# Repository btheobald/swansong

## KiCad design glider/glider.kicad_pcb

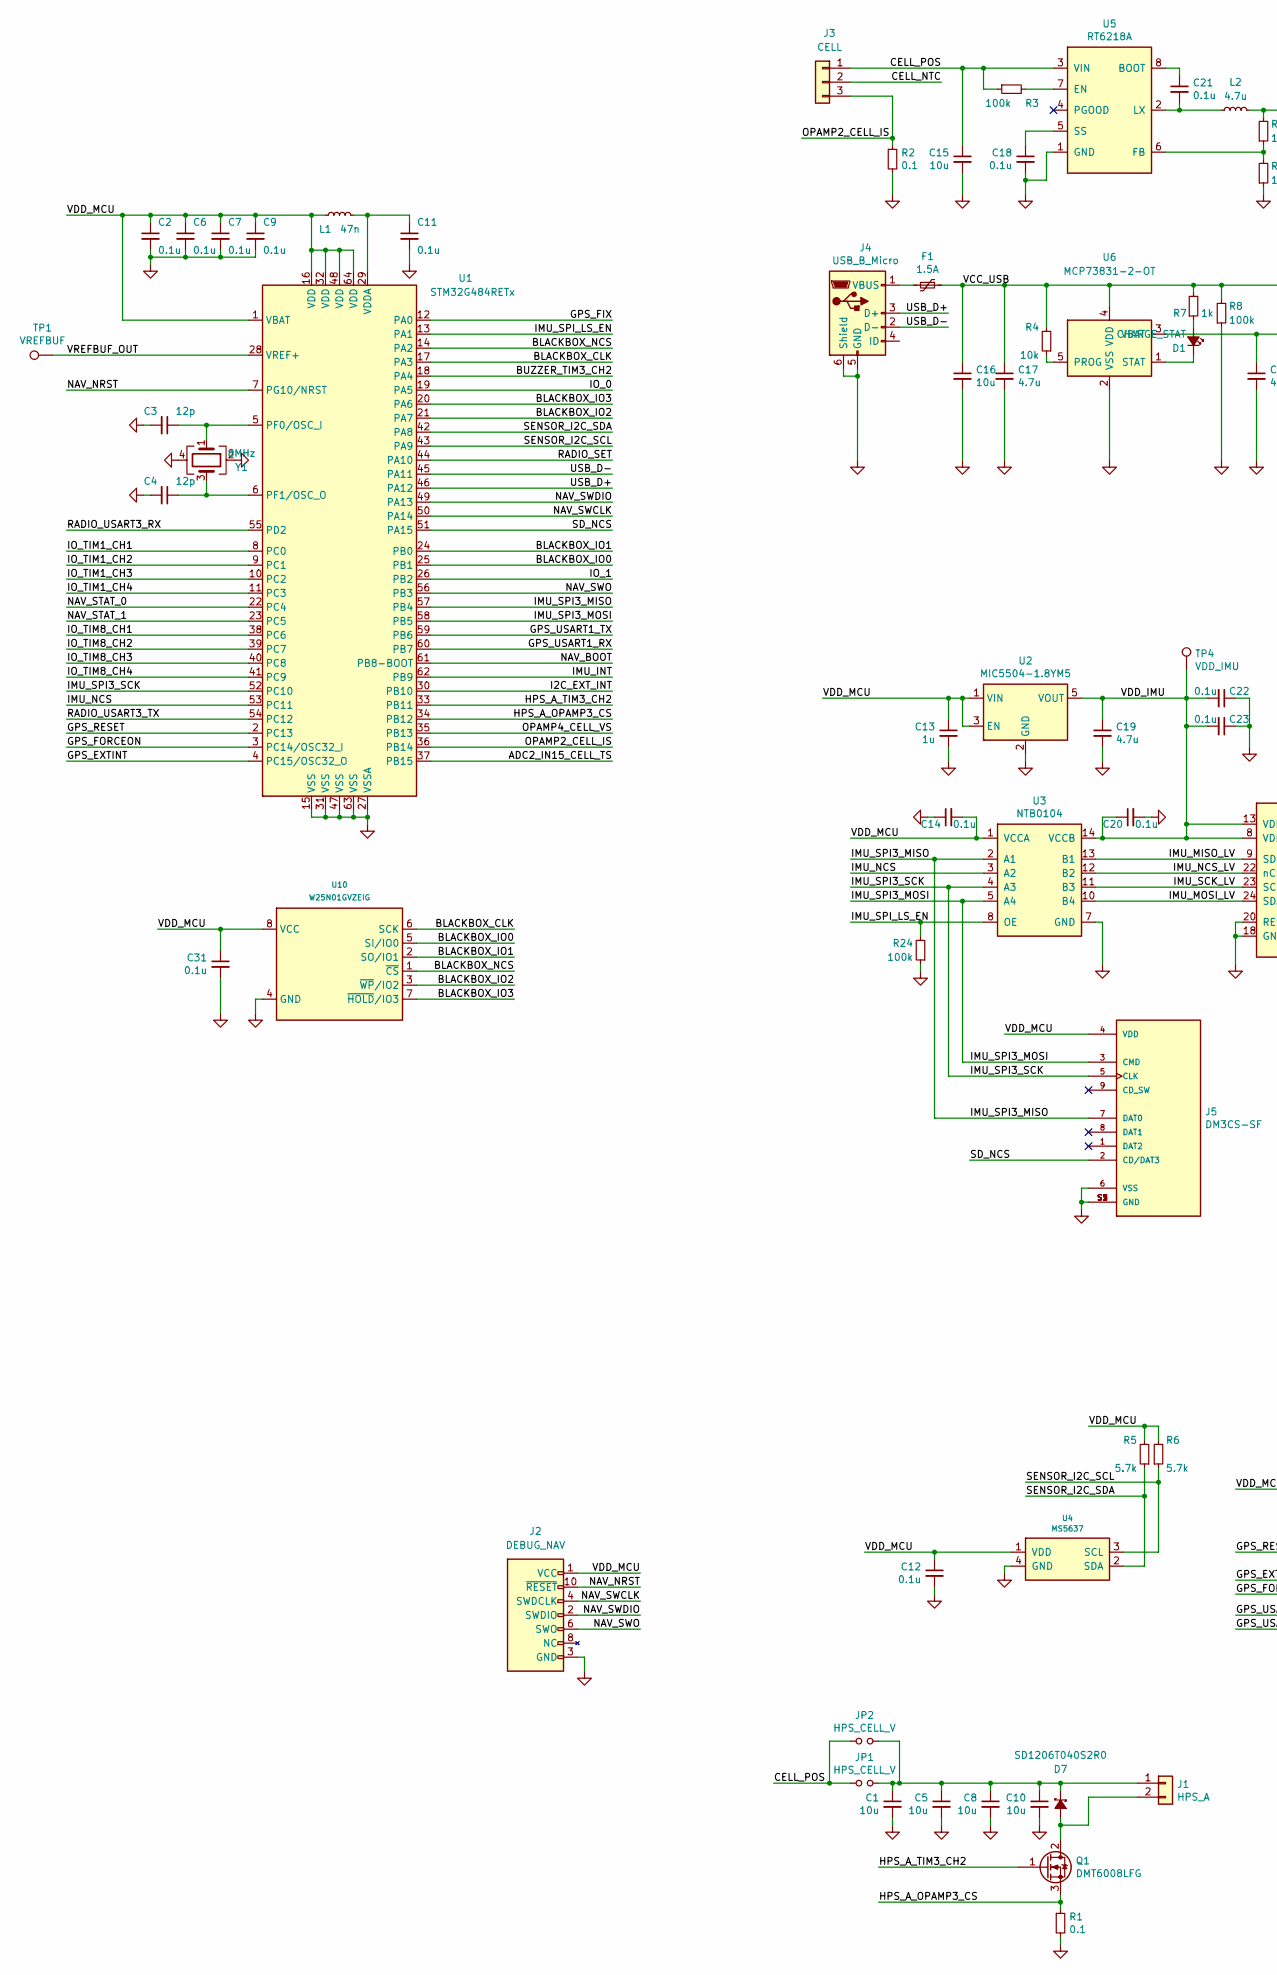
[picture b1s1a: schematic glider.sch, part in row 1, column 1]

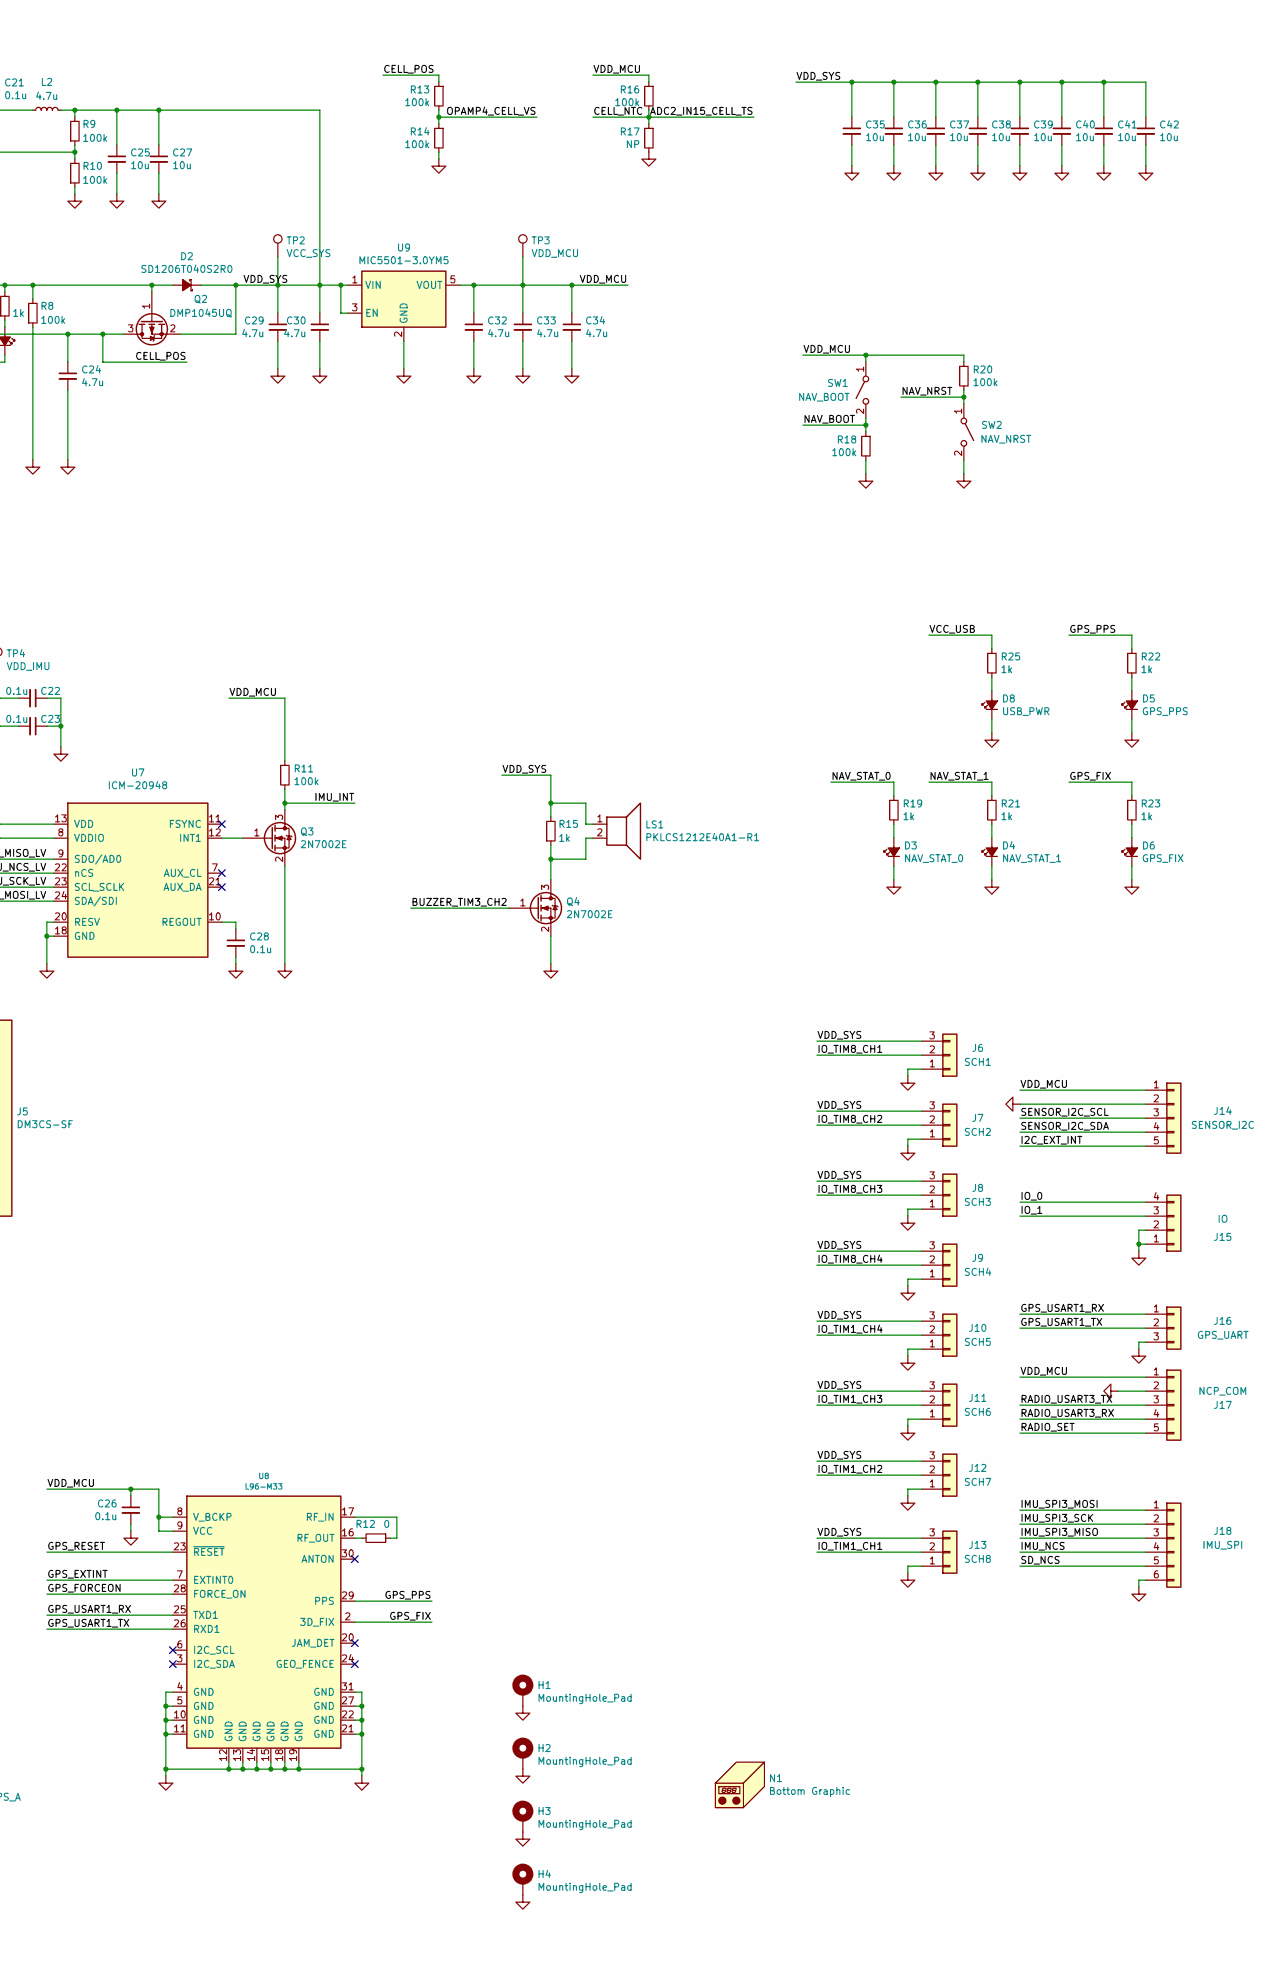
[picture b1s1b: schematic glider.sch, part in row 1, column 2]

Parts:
C1, C5, C8, C10: 10u; C_1206_3216Metric
C2, C6, C7, C9, C11, C12, C14, C18, C20, C21, C22, C23, C26, C28, C31: 0.1u; C_0402_1005Metric
C3, C4: 12p; C_0402_1005Metric
C13: 1u; C_0805_2012Metric
C15, C16, C25, C27, C35, C36, C37, C38, C39, C40, C41, C42: 10u; C_0805_2012Metric
C17, C19, C24, C29, C30, C32, C33, C34: 4.7u; C_0805_2012Metric
D1: CHARGE_STAT; LED_0603_1608Metric
D2, D7: SD1206T040S2R0; D_SOD-123
D3: NAV_STAT_0; LED_0603_1608Metric
D4: NAV_STAT_1; LED_0603_1608Metric
D5: GPS_PPS; LED_0603_1608Metric
D6: GPS_FIX; LED_0603_1608Metric
D8: USB_PWR; LED_0603_1608Metric
F1: 1.5A; R_1210_3225Metric
H1, H2, H3, H4: MountingHole_Pad; MountingHole_2.5mm_Pad_Via
J1: HPS_A; R_2816_7142Metric_Pad3.20x4.45mm_HandSolder
J2: DEBUG_NAV; PinHeader_2x05_P1.27mm_Vertical_SMD
J3: CELL; PinSocket_1x03_P2.54mm_Vertical
J4: USB_B_Micro; USB_Micro-B_Molex_47346-0001
J5: DM3CS-SF; HRS_DM3CS-SF; PARTREV n/a
J6: SCH1; PinHeader_1x03_P2.54mm_Vertical
J7: SCH2; PinHeader_1x03_P2.54mm_Vertical
J8: SCH3; PinHeader_1x03_P2.54mm_Vertical
J9: SCH4; PinHeader_1x03_P2.54mm_Vertical
J10: SCH5; PinHeader_1x03_P2.54mm_Vertical
J11: SCH6; PinHeader_1x03_P2.54mm_Vertical
J12: SCH7; PinHeader_1x03_P2.54mm_Vertical
J13: SCH8; PinHeader_1x03_P2.54mm_Vertical
J14: SENSOR_I2C; PinHeader_1x05_P2.54mm_Vertical
J15: IO; PinHeader_1x04_P1.27mm_Vertical
J16: GPS_UART; PinHeader_1x03_P1.27mm_Vertical
J17: NCP_COM; PinHeader_1x05_P2.54mm_Vertical
J18: IMU_SPI; PinHeader_1x06_P1.27mm_Vertical
JP1, JP2: HPS_CELL_V; SolderJumper-2_P1.3mm_Open_TrianglePad1.0x1.5mm
L1: 47n; L_0402_1005Metric
L2: 4.7u; L_Bourns-SRN4018
LS1: PKLCS1212E40A1-R1; PKLCS1212
N1: Bottom Graphic; boardartswift
Q1: DMT6008LFG; Diodes_PowerDI3333-8
Q2: DMP1045UQ; SOT-23
Q3, Q4: 2N7002E; SOT-23
R1, R2: 0.1; R_1210_3225Metric
R3, R8, R9, R10, R11, R13, R14, R16, R18, R20, R24: 100k; R_0603_1608Metric
R4: 10k; R_0603_1608Metric
R5, R6: 5.7k; R_0603_1608Metric
R7, R15, R19, R21, R22, R23, R25: 1k; R_0603_1608Metric
R12: 0; R_0402_1005Metric
R17: NP; R_0603_1608Metric
SW1: NAV_BOOT; SW_SPST_PTS810
SW2: NAV_NRST; SW_SPST_PTS810
TP1: VREFBUF; TestPoint_THTPad_D1.0mm_Drill0.5mm
TP2: VCC_SYS; TestPoint_THTPad_D1.0mm_Drill0.5mm
TP3: VDD_MCU; TestPoint_THTPad_D1.0mm_Drill0.5mm
TP4: VDD_IMU; TestPoint_THTPad_D1.0mm_Drill0.5mm
U1: STM32G484RETx; LQFP-64_10x10mm_P0.5mm
U2: MIC5504-1.8YM5; SOT-23-5
U3: NTB0104; WQFN-14-1EP_2.5x3mm_P0.5mm_EP1.45x1.00mm
U4: MS5637; QFN-4_3x3_Pitch2mm
U5: RT6218A; SOT-23-8
U6: MCP73831-2-OT; SOT-23-5
U7: ICM-20948; QFN-24-1EP_3x3mm_P0.4mm_EP1.75x1.6mm
U8: L96-M33; L96
U9: MIC5501-3.0YM5; SOT-23-5
U10: W25N01GVZEIG; WSON-8x6mm-Pad-3.4x4.3mm
Y1: 8MHz; Crystal_SMD_SeikoEpson_FA238-4Pin_3.2x2.5mm

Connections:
/ADC2_IN15_CELL_TS: J3.2, R16.2, R17.1, U1.37 (PB15)
/BLACKBOX_CLK: U1.17 (PA3), U10.6 (SCK)
/BLACKBOX_IO0: U1.25 (PB1), U10.5 (SI/IO0)
/BLACKBOX_IO1: U1.24 (PB0), U10.2 (SO/IO1)
/BLACKBOX_IO2: U1.21 (PA7), U10.3 (~WP~/IO2)
/BLACKBOX_IO3: U1.20 (PA6), U10.7 (~HOLD~/IO3)
/BLACKBOX_NCS: U1.14 (PA2), U10.1 (~CS)
/BUZZER_TIM3_CH2: Q4.1 (G), U1.18 (PA4)
/CELL_POS: C15.1, C24.1, J3.1, JP1.1, JP2.1, Q2.3 (D), R3.1, R13.1, U5.3 (VIN), U6.3 (VBAT)
/GPS_EXTINT: U1.4 (PC15/OSC32_O), U8.7 (EXTINT0)
/GPS_FIX: R23.1, U1.12 (PA0), U8.2 (3D_FIX)
/GPS_FORCEON: U1.3 (PC14/OSC32_I), U8.28 (FORCE_ON)
/GPS_PPS: R22.1, U8.29 (PPS)
/GPS_RESET: U1.2 (PC13), U8.23 (~RESET)
/GPS_USART1_RX: J16.1, U1.60 (PB7), U8.25 (TXD1)
/GPS_USART1_TX: J16.2, U1.59 (PB6), U8.26 (RXD1)
/HPS_A_OPAMP3_CS: Q1.3 (S), R1.1, U1.34 (PB12)
/HPS_A_TIM3_CH2: Q1.1 (G), U1.33 (PB11)
/I2C_EXT_INT: J14.5, U1.30 (PB10)
/IMU_INT: Q3.3 (D), R11.2, U1.62 (PB9)
/IMU_MISO_LV: U3.13 (B1), U7.9 (SDO/AD0)
/IMU_MOSI_LV: U3.10 (B4), U7.24 (SDA/SDI)
/IMU_NCS: J18.4, U1.53 (PC11), U3.3 (A2)
/IMU_NCS_LV: U3.12 (B2), U7.22 (nCS)
/IMU_SCK_LV: U3.11 (B3), U7.23 (SCL_SCLK)
/IMU_SPI3_MISO: J5.7 (DAT0), J18.3, U1.57 (PB4), U3.2 (A1)
/IMU_SPI3_MOSI: J5.3 (CMD), J18.1, U1.58 (PB5), U3.5 (A4)
/IMU_SPI3_SCK: J5.5 (CLK), J18.2, U1.52 (PC10), U3.4 (A3)
/IMU_SPI_LS_EN: R24.2, U1.13 (PA1), U3.8 (OE)
/IO_0: J15.4, U1.19 (PA5)
/IO_1: J15.3, U1.26 (PB2)
/IO_TIM1_CH1: J13.2, U1.8 (PC0)
/IO_TIM1_CH2: J12.2, U1.9 (PC1)
/IO_TIM1_CH3: J11.2, U1.10 (PC2)
/IO_TIM1_CH4: J10.2, U1.11 (PC3)
/IO_TIM8_CH1: J6.2, U1.38 (PC6)
/IO_TIM8_CH2: J7.2, U1.39 (PC7)
/IO_TIM8_CH3: J8.2, U1.40 (PC8)
/IO_TIM8_CH4: J9.2, U1.41 (PC9)
/NAV_BOOT: R18.1, SW1.2 (B), U1.61 (PB8-BOOT)
/NAV_NRST: J2.10 (~RESET~), R20.2, SW2.1 (A), U1.7 (PG10/NRST)
/NAV_STAT_0: R19.1, U1.22 (PC4)
/NAV_STAT_1: R21.1, U1.23 (PC5)
/NAV_SWCLK: J2.4 (SWDCLK), U1.50 (PA14)
/NAV_SWDIO: J2.2 (SWDIO), U1.49 (PA13)
/NAV_SWO: J2.6 (SWO), U1.56 (PB3)
/OPAMP2_CELL_IS: J3.3, R2.1, U1.36 (PB14)
/OPAMP4_CELL_VS: R13.2, R14.1, U1.35 (PB13)
/RADIO_SET: J17.5, U1.44 (PA10)
/RADIO_USART3_RX: J17.4, U1.55 (PD2)
/RADIO_USART3_TX: J17.3, U1.54 (PC12)
/SD_NCS: J5.2 (CD/DAT3), J18.5, U1.51 (PA15)
/SENSOR_I2C_SCL: J14.3, R6.1, U1.43 (PA9), U4.3 (SCL)
/SENSOR_I2C_SDA: J14.4, R5.1, U1.42 (PA8), U4.2 (SDA)
/USB_D+: J4.3 (D+), U1.46 (PA12)
/USB_D-: J4.2 (D-), U1.45 (PA11)
/VCC_USB: C16.1, C17.1, D2.2 (A), F1.1, Q2.1 (G), R4.2, R7.2, R8.2, R25.1, U6.4 (VDD)
/VDD_IMU: C19.1, C20.1, C22.2, C23.2, TP4.1, U2.5 (VOUT), U3.14 (VCCB), U7.8 (VDDIO), U7.13 (VDD)
/VDD_MCU: C2.1, C6.1, C7.1, C9.1, C12.1, C13.1, C14.2, C26.1, C31.1, C32.1, C33.1, C34.1, J2.1 (VCC), J5.4 (VDD), J14.1, J17.1, L1.2, R5.2, R6.2, R11.1, R16.1, R20.1, SW1.1 (A), TP3.1, U1.1 (VBAT), U1.16 (VDD), U1.32 (VDD), U1.48 (VDD), U1.64 (VDD), U2.1 (VIN), U2.3 (EN), U3.1 (VCCA), U4.1 (VDD), U8.8 (V_BCKP), U8.9 (VCC), U9.5 (VOUT), U10.8 (VCC)
/VDD_SYS: C25.1, C27.1, C29.1, C30.1, C35.1, C36.1, C37.1, C38.1, C39.1, C40.1, C41.1, C42.1, D2.1 (K), J6.3, J7.3, J8.3, J9.3, J10.3, J11.3, J12.3, J13.3, L2.1, LS1.1, Q2.2 (S), R9.2, R15.2, TP2.1, U9.1 (VIN), U9.3 (EN)
/VREFBUF_OUT: TP1.1, U1.28 (VREF+)
GND: C1.2, C2.2, C3.2, C4.2, C5.2, C6.2, C7.2, C8.2, C9.2, C10.2, C11.2, C12.2, C13.2, C14.1, C15.2, C16.2, C17.2, C18.2, C19.2, C20.2, C22.1, C23.1, C24.2, C25.2, C26.2, C27.2, C28.2, C29.2, C30.2, C31.2, C32.2, C33.2, C34.2, C35.2, C36.2, C37.2, C38.2, C39.2, C40.2, C41.2, C42.2, D3.1 (K), D4.1 (K), D5.1 (K), D6.1 (K), D8.1 (K), H1.1, H2.1, H3.1, H4.1, J2.3 (GND), J2.5 (GND), J2.9 (GND), J4.5 (GND), J4.6 (Shield), J5.6 (VSS), J5.S1 (GND), J5.S2 (GND), J5.S3 (GND), J5.S5 (GND), J6.1, J7.1, J8.1, J9.1, J10.1, J11.1, J12.1, J13.1, J14.2, J15.1, J15.2, J16.3, J17.2, J18.6, Q3.2 (S), Q4.2 (S), R1.2, R2.2, R8.1, R10.1, R14.2, R17.2, R18.2, R24.1, SW2.2 (B), U1.15 (VSS), U1.27 (VSSA), U1.31 (VSS), U1.47 (VSS), U1.63 (VSS), U2.2 (GND), U3.7 (GND), U3.15 (GND), U4.4 (GND), U5.1 (GND), U6.2 (VSS), U7.18 (GND), U7.20 (RESV), U8.4 (GND), U8.5 (GND), U8.10 (GND), U8.11 (GND), U8.12 (GND), U8.13 (GND), U8.14 (GND), U8.15 (GND), U8.18 (GND), U8.19 (GND), U8.21 (GND), U8.22 (GND), U8.27 (GND), U8.31 (GND), U9.2 (GND), U10.4 (GND), U10.9 (GND), Y1.2, Y1.4
unnamed: C1.1, C5.1, C8.1, C10.1, D7.1 (K), J1.1, JP1.2, JP2.2
unnamed: C3.1, U1.5 (PF0/OSC_I), Y1.1
unnamed: C4.1, U1.6 (PF1/OSC_O), Y1.3
unnamed: C11.1, L1.1, U1.29 (VDDA)
unnamed: C18.1, U5.5 (SS)
unnamed: C21.1, U5.8 (BOOT)
unnamed: C21.2, L2.2, U5.2 (LX)
unnamed: C28.1, U7.10 (REGOUT)
unnamed: D1.1 (K), U6.1 (STAT)
unnamed: D1.2 (A), R7.1
unnamed: D3.2 (A), R19.2
unnamed: D4.2 (A), R21.2
unnamed: D5.2 (A), R22.2
unnamed: D6.2 (A), R23.2
unnamed: D7.2 (A), J1.2, Q1.2 (D)
unnamed: D8.2 (A), R25.2
unnamed: F1.2, J4.1 (VBUS)
unnamed: LS1.2, Q4.3 (D), R15.1
unnamed: Q3.1 (G), U7.12 (INT1)
unnamed: R3.2, U5.7 (EN)
unnamed: R4.1, U6.5 (PROG)
unnamed: R9.1, R10.2, U5.6 (FB)
unnamed: R12.1, U8.17 (RF_IN)
unnamed: R12.2, U8.16 (RF_OUT)

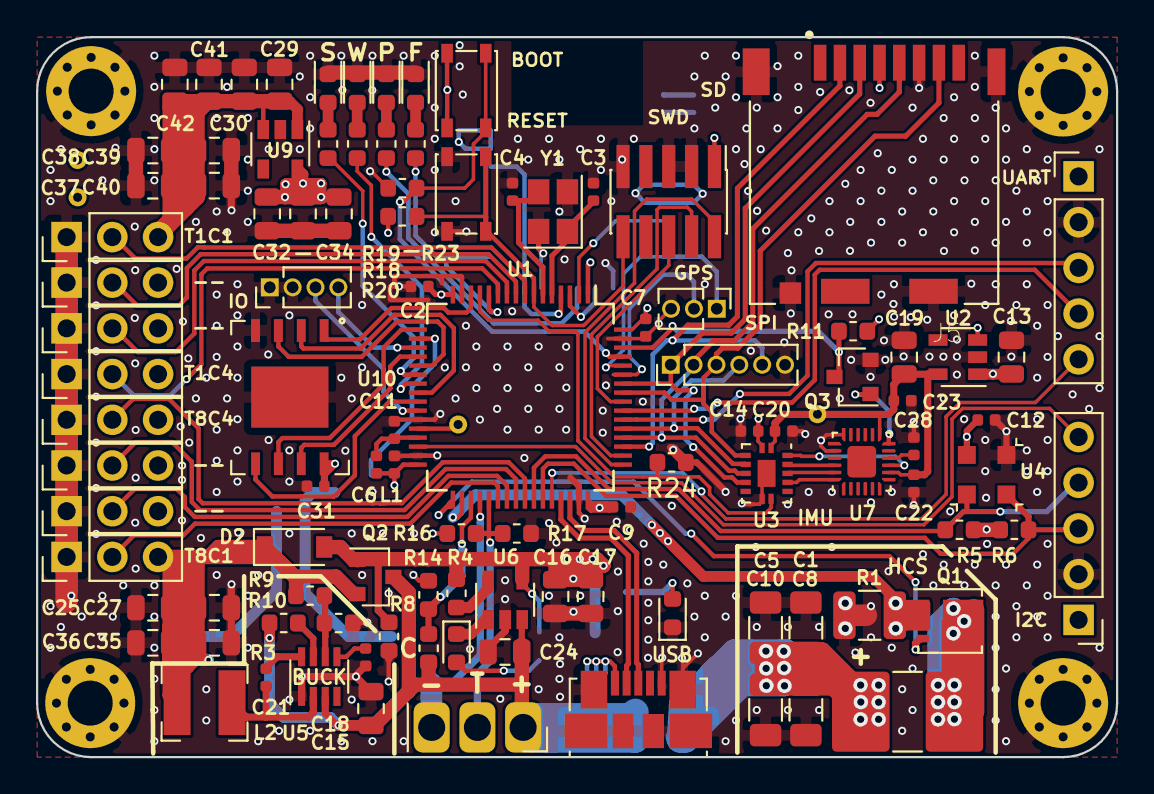
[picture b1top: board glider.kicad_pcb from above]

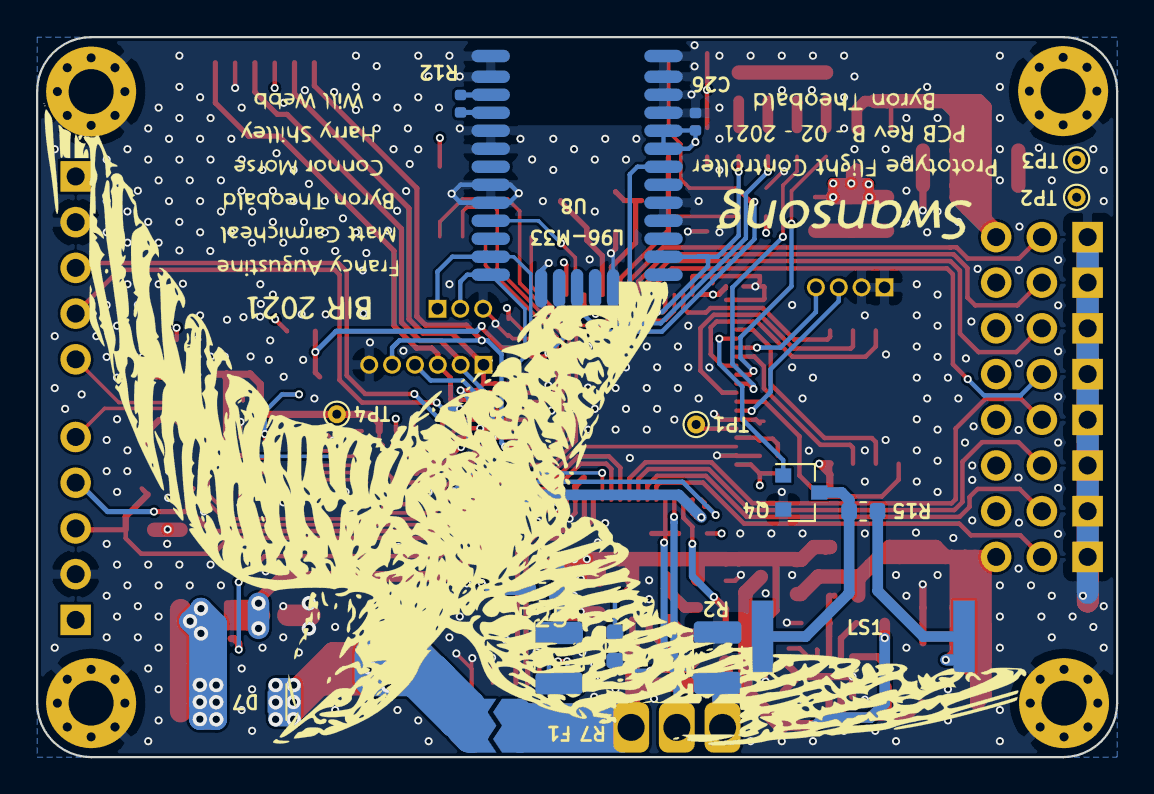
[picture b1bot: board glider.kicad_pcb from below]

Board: 4 copper layers, 60.0 x 40.0 mm, 125 parts (18 on the bottom side), 86 nets.

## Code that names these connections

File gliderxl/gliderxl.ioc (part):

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Mcu.Name=STM32G484RETx
Mcu.Package=LQFP64
Mcu.UserName=STM32G484RETx
PA0.GPIOParameters=GPIO_Label
PA0.GPIO_Label=GPS_FIX
PA0.Signal=GPIO_Input
PA1.GPIOParameters=GPIO_Label
PA1.GPIO_Label=IMU_SPI_LS_EN
PA1.Signal=GPIO_Output
PA10.GPIOParameters=GPIO_Label
PA10.GPIO_Label=RADIO_SET
PA10.Signal=GPIO_Output
PA11.Mode=Device
PA11.Signal=USB_DM
PA12.Mode=Device
PA12.Signal=USB_DP
PA13.Mode=Trace_Asynchronous_SW
PA13.Signal=SYS_JTMS-SWDIO
PA14.Mode=Trace_Asynchronous_SW
PA14.Signal=SYS_JTCK-SWCLK
PA15.GPIOParameters=GPIO_Label
PA15.GPIO_Label=SD_NCS
PA15.Signal=GPIO_Output
PA2.GPIOParameters=GPIO_Speed,GPIO_PuPd
PA2.GPIO_PuPd=GPIO_PULLUP
PA2.GPIO_Speed=GPIO_SPEED_FREQ_VERY_HIGH
PA2.Mode=Single Bank 1
PA2.Signal=QUADSPI1_BK1_NCS
PA3.GPIOParameters=GPIO_Speed,GPIO_PuPd
PA3.GPIO_PuPd=GPIO_NOPULL
PA3.GPIO_Speed=GPIO_SPEED_FREQ_VERY_HIGH
PA3.Mode=Single Bank 1
PA3.Signal=QUADSPI1_CLK
PA4.GPIOParameters=GPIO_Label
PA4.GPIO_Label=BUZZER_DAC
PA4.Signal=GPIO_Output
PA5.Mode=PGA_Internally_Connected
PA5.Signal=OPAMP2_VINM0
PA6.GPIOParameters=GPIO_Speed,GPIO_PuPd
PA6.GPIO_PuPd=GPIO_NOPULL
PA6.GPIO_Speed=GPIO_SPEED_FREQ_VERY_HIGH
PA6.Mode=Single Bank 1
PA6.Signal=QUADSPI1_BK1_IO3
PA7.GPIOParameters=GPIO_Speed
PA7.GPIO_Speed=GPIO_SPEED_FREQ_VERY_HIGH
PA7.Mode=Single Bank 1
PA7.Signal=QUADSPI1_BK1_IO2
PA8.GPIOParameters=GPIO_Label
PA8.GPIO_Label=SENSOR_I2C2_SDA
PA8.Mode=I2C
PA8.Signal=I2C2_SDA
PA9.GPIOParameters=GPIO_Label
PA9.GPIO_Label=SENSOR_I2C2_SCL
PA9.Mode=I2C
PA9.Signal=I2C2_SCL
PB0.GPIOParameters=GPIO_Speed
PB0.GPIO_Speed=GPIO_SPEED_FREQ_VERY_HIGH
PB0.Mode=Single Bank 1
PB0.Signal=QUADSPI1_BK1_IO1
PB1.GPIOParameters=GPIO_Speed
PB1.GPIO_Speed=GPIO_SPEED_FREQ_VERY_HIGH
PB1.Mode=Single Bank 1
PB1.Signal=QUADSPI1_BK1_IO0
PB11.GPIOParameters=GPIO_Label
PB11.GPIO_Label=HPS_A_TIM2_CH4
PB11.Signal=S_TIM2_CH4
PB12.GPIOParameters=GPIO_Label
PB12.GPIO_Label=HPS Current Sense A
PB12.Signal=OPAMP6_VINP
PB13.GPIOParameters=GPIO_Label
PB13.GPIO_Label=Battery Voltage Sense
PB13.Mode=Follower_Internally_Connected
PB13.Signal=OPAMP4_VINP
PB14.GPIOParameters=GPIO_Label
PB14.GPIO_Label=Battery Current Sense
PB14.Mode=PGA_Internally_Connected
PB14.Signal=OPAMP2_VINP
PB2.GPIOParameters=GPIO_Label
PB2.GPIO_Label=I2C_EXT_INT
PB2.Signal=GPIO_Input
PB3.Mode=Trace_Asynchronous_SW
PB3.Signal=SYS_JTDO-SWO
PB4.Mode=Full_Duplex_Master
PB4.Signal=SPI3_MISO
PB5.Mode=Full_Duplex_Master
PB5.Signal=SPI3_MOSI
PB6.GPIOParameters=GPIO_Label
PB6.GPIO_Label=GPS_USART1_TX
PB6.Mode=Asynchronous
PB6.Signal=USART1_TX
PB6.Stacked=true
PB7.GPIOParameters=GPIO_Label
PB7.GPIO_Label=GPS_USART1_RX
PB7.Mode=Asynchronous
PB7.Signal=USART1_RX
PB7.Stacked=true
PB8-BOOT0.GPIOParameters=GPIO_Label
PB8-BOOT0.GPIO_Label=USER_BTN
PB8-BOOT0.Signal=GPIO_Input
PB9.GPIOParameters=GPIO_Label
PB9.GPIO_Label=IMU_INT
PB9.Signal=GPIO_Output
PC0.Signal=S_TIM1_CH1
PC0.Stacked=true
PC1.Signal=S_TIM1_CH2
PC1.Stacked=true
PC10.Mode=Full_Duplex_Master
PC10.Signal=SPI3_SCK
PC11.GPIOParameters=PinState,GPIO_Label
PC11.GPIO_Label=IMU_NCS
PC11.PinState=GPIO_PIN_SET
PC11.Signal=GPIO_Output
PC12.GPIOParameters=GPIO_Label
PC12.GPIO_Label=RADIO_UART5_TX
PC12.Mode=Asynchronous
PC12.Signal=UART5_TX
PC13.GPIOParameters=GPIO_Label
PC13.GPIO_Label=GPS_RESET
PC13.Signal=GPIO_Output
PC14-OSC32_IN.GPIOParameters=GPIO_Label
PC14-OSC32_IN.GPIO_Label=GPS_FORCEON
PC14-OSC32_IN.Signal=GPIO_Output
PC15-OSC32_OUT.GPIOParameters=GPIO_Label
PC15-OSC32_OUT.GPIO_Label=GPS_EXT_INT
PC15-OSC32_OUT.Signal=GPIO_Output
PC2.Signal=S_TIM1_CH3
PC2.Stacked=true
PC3.Signal=S_TIM1_CH4
PC4.GPIOParameters=GPIO_Label
PC4.GPIO_Label=NAV_STAT_0
PC4.Signal=GPIO_Output
PC5.GPIOParameters=GPIO_Label
PC5.GPIO_Label=NAV_STAT_1
PC5.Signal=GPIO_Output
PC6.Signal=S_TIM8_CH1
PC6.Stacked=true
PC7.Signal=S_TIM8_CH2
PC7.Stacked=true
PC8.Signal=S_TIM8_CH3
PC8.Stacked=true
PC9.Signal=S_TIM8_CH4
PC9.Stacked=true
PD2.GPIOParameters=GPIO_Label
PD2.GPIO_Label=RADIO_UART5_RX
PD2.Mode=Asynchronous
PD2.Signal=UART5_RX
PF0-OSC_IN.Mode=HSE-External-Oscillator
PF0-OSC_IN.Signal=RCC_OSC_IN
PF1-OSC_OUT.Mode=HSE-External-Oscillator
PF1-OSC_OUT.Signal=RCC_OSC_OUT
RCC.HSE_VALUE=8000000
RCC.SYSCLKFreq_VALUE=170000000
RCC.SYSCLKSource=RCC_SYSCLKSOURCE_PLLCLK
board=custom

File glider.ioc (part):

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PA6.Mode=Single Bank 1
Mcu.UserName=STM32G473CETx
PA0.GPIO_Label=GPS_EXTINT
PA11.Mode=Device
PA3.GPIOParameters=GPIO_Label
PA6.GPIO_Label=BLACKBOX_IO3
PB0.GPIO_Label=BLACKBOX_IO1
PC13.GPIO_Label=CTRL_INT_I
PB11.Signal=GPIO_Output
PB13.Signal=SPI2_SCK
PB15.Signal=SPI2_MOSI
PA2.GPIOParameters=GPIO_Label
PC15-OSC32_OUT.GPIO_Label=GPS_RESET
RCC.SYSCLKSource=RCC_SYSCLKSOURCE_PLLCLK
PA12.Signal=USB_DP
PB6.Signal=USART1_TX
RCC.HSE_VALUE=16000000
PB2.Signal=GPIO_Input
PB3.Mode=Full_Duplex_Master
PB12.GPIO_Label=IMU_A_NSS
PB0.GPIOParameters=GPIO_Label
PA1.GPIOParameters=GPIO_Label
PB4.Mode=Full_Duplex_Master
PA14.Mode=Serial_Wire
PB14.Mode=Full_Duplex_Slave
PB1.GPIO_Label=BLACKBOX_IO0
PB5.Mode=Full_Duplex_Master
PA10.GPIO_Label=TOF_EN
PB7.Signal=USART1_RX
PA8.Signal=I2C2_SDA
PC14-OSC32_IN.GPIOParameters=GPIO_Label
PA0.Signal=GPIO_Output
Mcu.Package=LQFP48
PB9.Signal=GPIO_Output
PB1.Signal=QUADSPI1_BK1_IO0
PA6.Signal=QUADSPI1_BK1_IO3
PA2.GPIO_Label=BLACKBOX_NCS
PA10.Signal=GPIO_Output
PA15.Signal=SPI3_NSS
PA5.GPIOParameters=GPIO_Label
PC14-OSC32_IN.GPIO_Label=GPS_FIX
PB10.GPIOParameters=GPIO_Label
PB13.Mode=Full_Duplex_Slave
PC15-OSC32_OUT.GPIOParameters=GPIO_Label
PF1-OSC_OUT.Mode=HSE-External-Oscillator
PA4.GPIO_Label=GPS_FORCEON
PF1-OSC_OUT.Signal=RCC_OSC_OUT
PB4.Signal=SPI3_MISO
PA3.Signal=QUADSPI1_CLK
PA6.GPIOParameters=GPIO_Label
PA7.Mode=Single Bank 1
PB9.GPIO_Label=NAV_INT_O
PC13.Signal=SYS_WKUP2
PB11.GPIO_Label=IMU_M_NSS
PC14-OSC32_IN.Signal=GPIO_Input
PB9.GPIOParameters=GPIO_Label
PA3.Mode=Single Bank 1
PA13.Signal=SYS_JTMS-SWDIO
PA9.Mode=I2C
PB10.GPIO_Label=IMU_A_INT
PB2.GPIOParameters=GPIO_Label
PA9.Signal=I2C2_SCL
PB11.GPIOParameters=GPIO_Label
PC15-OSC32_OUT.Signal=GPIO_Output
PA1.Signal=OPAMP1_VINP
PF0-OSC_IN.Mode=HSE-External-Oscillator
PB10.Signal=GPIO_Input
PB14.Signal=SPI2_MISO
PA5.Signal=GPIO_Output
PB0.Mode=Single Bank 1
board=custom
PB15.Mode=Full_Duplex_Slave
PC13.GPIOParameters=GPIO_Label
PA1.GPIO_Label=SYS_CURRENT
PA10.GPIOParameters=GPIO_Label
PA4.GPIOParameters=GPIO_Label
PC13.Mode=SYS_WakeUp1
PA13.Mode=Serial_Wire
Mcu.Name=STM32G473C(B-C-E)Tx
PA2.Signal=QUADSPI1_BK1_NCS
PB3.Signal=SPI3_SCK
PA4.Signal=GPIO_Output
RCC.SYSCLKFreq_VALUE=500000000
PB5.Signal=SPI3_MOSI
PA7.GPIO_Label=BLACKBOX_IO2
PA12.Mode=Device
PA5.GPIO_Label=NAV_STAT_0
PA11.Signal=USB_DM
PA14.Signal=SYS_JTCK-SWCLK
PB2.GPIO_Label=IMU_M_INT
PA0.GPIOParameters=GPIO_Label
PB1.Mode=Single Bank 1
PA2.Mode=Single Bank 1
PA8.Mode=I2C
PF0-OSC_IN.Signal=RCC_OSC_IN
PB0.Signal=QUADSPI1_BK1_IO1
PA7.GPIOParameters=GPIO_Label
PB12.GPIOParameters=GPIO_Label
PB12.Signal=GPIO_Input
PA3.GPIO_Label=BLACKBOX_CLK
PB1.GPIOParameters=GPIO_Label
PA7.Signal=QUADSPI1_BK1_IO2

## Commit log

2021-02-17 uploading files
2021-02-18 all components placed, initial board art
2021-02-23 final checkouts
2021-02-24 removed bt module again, shrunk board
2021-02-25 reved layout complete, silkscreen todo
2021-02-28 submitted to jlc
2021-03-01 design in manufacture
2021-03-29 bulk changes
2021-03-29 added gitignore
2021-03-29 removed build
2021-03-30 more work, logging data now
